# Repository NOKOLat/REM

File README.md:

# REM (Receiver Extension Module)
本システムはs.busを読み取り最大10chのPWMを出力するものである．
一般的なFutaba製受信機では，6ch程度のものが多くまたチャンネル数を増やすと重量が増加する問題があった．
Futaba製受信機で最軽量なものはR3206SBMで公称1g以下であり，s.busと6chのPWM出力が可能である．実用時にはサーボやESCへの電源の分配を外部で行う必要があり4g程度である．その他の受信機は6chで8g，8chで10g程度となっている．
本システムは10chで5gに収まる軽量なものである．

また，飛行ロボコン マルチコプター部門の自動投下に対応するためにADCポートを1つ設けている．

# 使い方
## 基板の解説
受信機やESC，サーボなどの接続図を示す．

受信機は図上方のピンヘッダーのうち左側3ピンを使用する．
ピン配置は左からGND，5V，S.Busである．

図右側にはESC,サーボ向けのPWM出力をするピンが10ch分ある．
図下側から順に1ch - 10chである．
従来の受信機と同様にESCを接続すると基板に電源が供給される．

図左側のPC及びシリアル変換モジュールはマイコンのプログラムの書き込みに使用する．
ピンヘッダーのピン配置は上からシリアル通信のRXとTX,GND,3.3V，BOOTである．
3.3Vに電源を接続する際は基板に5Vを入力してはならない．
シリアル通信のRX，TXはいずれもマイコンのRX，TXピンに接続されている．
RXピンに信号を入力し，TXピンから信号が出力される．

インジケーターとしてLEDが4つある．
LEDはPWM用のピンヘッダーに近い方から順に，5Vと3.3Vの電源確認および2つのマイコンの状態確認用である．

## PCとの接続
プログラムの書き込みには[STM32CubeProgrammer](https://www.st.com/ja/development-tools/stm32cubeprog.html)を使用する．
STのwebページよりダウンロードし，インストールする．

使用するものはPCとシリアル変換モジュール，5V電源供給のためのLiPoおよびESCである．
まず，シリアル変換モジュールと基板でシリアル通信の信号線 (RX,TX)とGNDの3線を接続する．
その後，タクトスイッチを押しながら5Vを接続する．
最後にPCとシリアル変換モジュールを接続する．

STM32CubeProgrammerを用いてマイコンに接続する．
まず，マイコンとの接続方法をUARTに設定する．
その後，UARTの設定を行う．
ポートは環境によって異なるので，各自の環境においてシリアル変換モジュールのポートを選択する．
ボーレートは経験的に56000以下で選択するとよい．
その他の項目は特に設定する必要はない．
以上ができたらconnectする．
エラーが出た際はエラーメッセージを確認して対処する．
よくあるトラブルは基板の電源投入時にスイッチを上手く押せていないことなので，電源を入れ直すと解決することがある．

## 初回セットアップ
ここでは，マイコンのプログラムに依存しない部分の設定をおこなう．
このステップを正しく実行しないと，プログラムの書き直しが不可能になるので確実に行う．

画面左のメニューから**OB**(Option bytes)を選択する．
**User Configuration**にある**nBOOT_SEL**および**nBOOT1**，**nBOOT0**のチェックが画像と同じになるように設定する．

同様に**NRST_MODE** を2に設定する．

以上でセットアップは完了である．

## プログラムの更新
画面左のメニューよりErasing & Programmingを選択する．
File Pathで実行ファイル (10chReceiver.elf) を選択する．
**Verify programming**と**Run after programming**にチェックを入れる．
**Start Programming**をクリックして，書き込みを開始する．
処理が終了し，Logに`Download verified successfully`と表示されていれば正常終了である．

実行ファイルはGithubのリリースよりダウンロードするか，ソースファイルをビルドして用意する．

## LEDの点滅パターン
プログラム起動時にLED1とLED2が点灯し起動処理が完了すると消灯するが，点灯時間がごく短時間であるため確認できないと思われる．
s.busのフレームを受信している間はLED2が高速で点滅する．
受信データがフェイルセーフもしくはフレームロストを示していたり，正常にデータを処理できない状態が続くとLED1がゆっくり点滅する．
また，s.busの受信ができない状態となったときもLED1がゆっくり点滅する．
したがって，LEDの点灯パターンを用いておおよそ下記のように判断できる．

|LED(Green)|LED(Red)|Stat|
|:--:|:--:|:--:|
|早い点滅|消灯|正常|
|遅い点滅|点灯|基板-受信機の接続に問題がある|
|早い点滅|点灯|受信機-プロポの通信に問題がある|

# ファームウェアのカスタマイズ
## PWMデューティー比レンジの設定
Futaba製RCサーボ向けのPWM出力とLED向けにデューティー比0%から100%の2種類を用意している．
設定は *user.h* にある`convertToPulseWidth()`で行う．
使用方法は実装を見てほしい．
RCサーボ向けのPWMとする場合は`CONVERT_TO_RC_PWM_WIDTH(sbusValue)`を使用する．
LED向けにデューティー比を0%から100%とする場合は`CONVERT_TO_LED_PWM_WIDTH(sbusValue)`を使用する．

## カスタムミキシング
*user.h* にある`mixer()`で行う．
ユーザーは`mixer()`を編集することにより，ミキシングや条件に応じた動作の変更をすることができる．

アナログ入力を使用する場合はadcValueを参照する．
ADCは0から3.3Vの入力を0から255のディジタル値に変換するように設定されているのでadcValueの値域は0から255となる．
フォトトランジスタとアナログ入力を使用することで，マルチコプター部門の自動投下に対応可能である．

# 基板
PCBデザインは *./PCB/* にある．

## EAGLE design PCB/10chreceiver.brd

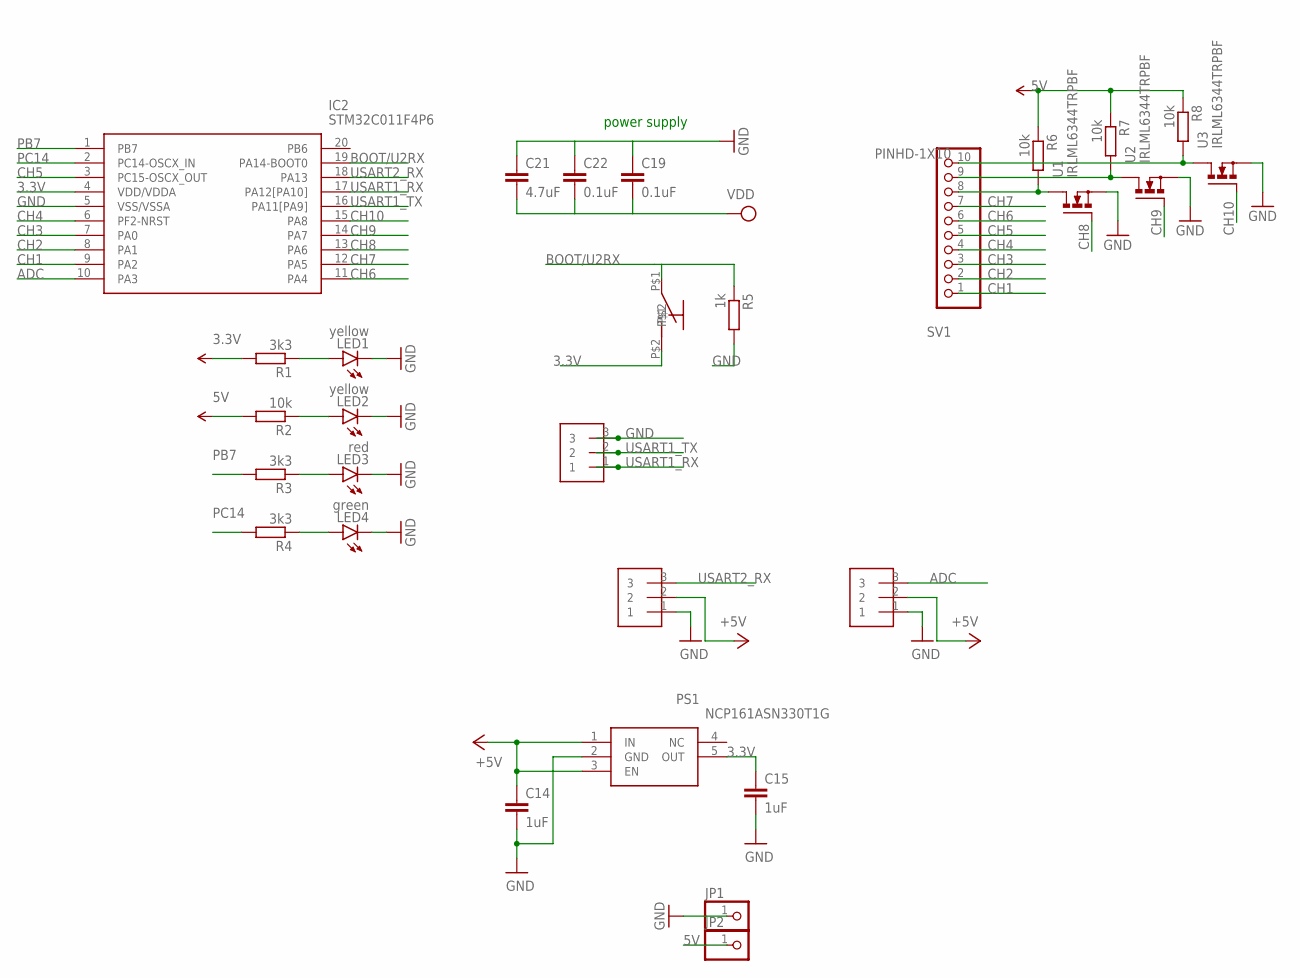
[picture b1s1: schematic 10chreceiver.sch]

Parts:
C14, C15: 1uF; C1608
C19, C22: 0.1uF; C1608
C21: 4.7uF; C1608
CN1, CN2, CN3: 1X3
IC2: STM32C011F4P6; SOP65P640X120-20N
JP1, JP2: PINHD-1X1; 1X01
LED1, LED2: yellow; CHIPLED_0603
LED3: red; CHIPLED_0603
LED4: green; CHIPLED_0603
PS1: NCP161ASN330T1G; SOT95P280X145-5N
R1, R3, R4: 3k3; R0603
R2, R6, R7, R8: 10k; R0603
R5: 1k; R0603
SV1: PINHD-1X10; 1X10-BIG
SW2: TSY3420-TACTSW
U1, U2, U3: IRLML6344TRPBF; SOT95P240X112-3N

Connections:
3.3V: C15.1, C19.2, C21.2, C22.2, IC2.4 (VDD/VDDA), PS1.5 (OUT), R1.2, SW2.P$2
5V: C14.1, CN2.2, CN3.2, JP2.1, PS1.1 (IN), PS1.3 (EN), R2.2, R6.1, R7.1, R8.1
ADC: CN2.3, IC2.10 (PA3)
BOOT/U2RX: IC2.19 (PA14-BOOT0), R5.1, SW2.P$1
CH1: IC2.9 (PA2), SV1.1
CH2: IC2.8 (PA1), SV1.2
CH3: IC2.7 (PA0), SV1.3
CH4: IC2.6 (PF2-NRST), SV1.4
CH5: IC2.3 (PC15-OSCX_OUT), SV1.5
CH6: IC2.11 (PA4), SV1.6
CH7: IC2.12 (PA5), SV1.7
CH8: IC2.13 (PA6), U1.1 (G)
CH9: IC2.14 (PA7), U2.1 (G)
CH10: IC2.15 (PA8), U3.1 (G)
GND: C14.2, C15.2, C19.1, C21.1, C22.1, CN1.3, CN2.1, CN3.1, IC2.5 (VSS/VSSA), JP1.1, LED1.C, LED2.C, LED3.C, LED4.C, PS1.2 (GND), R5.2, U1.2 (S), U2.2 (S), U3.2 (S)
unnamed: LED3.A, R3.1
unnamed: LED4.A, R4.1
unnamed: R6.2, SV1.8, U1.3 (D)
unnamed: LED1.A, R1.1
unnamed: R7.2, SV1.9, U2.3 (D)
unnamed: R8.2, SV1.10, U3.3 (D)
unnamed: LED2.A, R2.1
PB7: IC2.1 (PB7), R3.2
PC14: IC2.2 (PC14-OSCX_IN), R4.2
USART1_RX: CN1.1, IC2.17 (PA12[PA10])
USART1_TX: CN1.2, IC2.16 (PA11[PA9])
USART2_RX: CN3.3, IC2.18 (PA13)

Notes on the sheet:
power supply

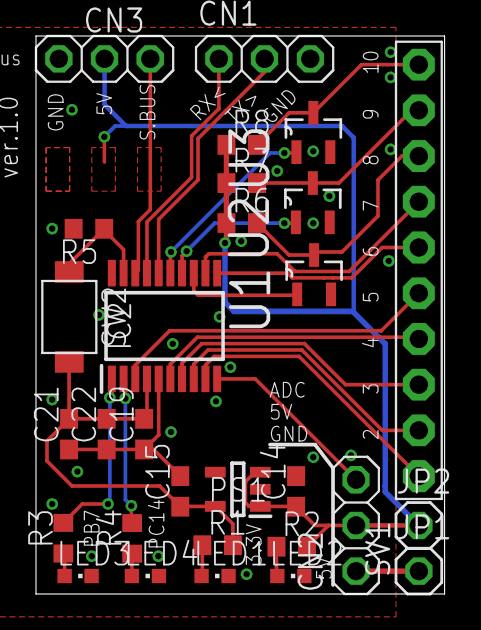
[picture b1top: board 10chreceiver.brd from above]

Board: 2 copper layers, 22.7 x 31.0 mm, 29 parts (0 on the bottom side), 27 nets.

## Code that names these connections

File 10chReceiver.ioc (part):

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Mcu.Name=STM32C011F(4-6)Px
Mcu.Package=TSSOP20
Mcu.UserName=STM32C011F4Px
PA0.Signal=S_TIM16_CH1
PA1.GPIOParameters=GPIO_ModeDefaultPP,GPIO_Speed,PinState,GPIO_PuPd
PA1.GPIO_ModeDefaultPP=GPIO_MODE_AF_PP
PA1.GPIO_PuPd=GPIO_NOPULL
PA1.GPIO_Speed=GPIO_SPEED_FREQ_LOW
PA1.PinState=GPIO_PIN_RESET
PA1.Signal=S_TIM1_CH2
PA10\ [PA12].Mode=Asynchronous
PA10\ [PA12].Signal=USART1_RX
PA13.Mode=Asynchronous
PA13.Signal=USART2_RX
PA14-BOOT0.Mode=Asynchronous
PA14-BOOT0.Signal=USART2_TX
PA2.Signal=S_TIM1_CH3
PA3.Mode=IN3
PA3.Signal=ADC1_IN3
PA4.Signal=S_TIM14_CH1
PA5.Signal=S_TIM1_CH1
PA6.Signal=S_TIM3_CH1
PA7.Signal=S_TIM3_CH2
PA8.Signal=S_TIM3_CH4
PA9\ [PA11].Mode=Asynchronous
PA9\ [PA11].Signal=USART1_TX
PB7.Signal=GPIO_Output
PC14-OSCX_IN\ (PC14).Signal=GPIO_Output
PC15-OSCX_OUT\ (PC15).Signal=S_TIM3_CH3
PF2-NRST.Signal=S_TIM1_CH4
RCC.HSE_VALUE=8000000
RCC.SYSCLKFreq_VALUE=48000000
board=custom

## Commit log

2024-08-16 とりあえず動いた
2024-08-16 refactor
2024-11-22 fix bug
2025-05-25 bug fix
2025-05-25 update user action for cross environments
2025-05-25 update module
2025-05-25 debugした
2025-05-27 write README.md
2025-05-29 Create LICENSE
2025-06-09 start development of v2
2025-06-09 finish coding
2025-06-28 一般班向けのデバック終了
2025-06-28 add MCU_OB (Option Bytes) configuration file
2025-07-01 adc関連のdebug 飛行機向けの動作確認
2025-08-16 update lib
2025-08-16 debug
2025-08-16 カスタマイズ
2025-09-01 custom
2025-09-03 プロポ - 受信機の通信が切断されたときフェイルセーフが機能するように修正
2025-09-04 arranged
2025-09-09 LED点灯用に9, 10chのデューティー比レンジを変更
2025-09-21 手動モードでの赤外線検知後にホールド
2025-10-01 #8 PWMパルス幅の切り替え
2025-10-01 editing
2025-10-05 デューティー比の切り替えについて書ききった
2025-10-05 remove comment-out
2025-10-05 PCBについて追記
2025-10-05 upload PCB design
2025-10-05 sbusライブラリの更新
2025-10-05 rename ioc file

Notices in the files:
parts and their libraries:
SparkFun-PowerSymbols: Licensing: Creative Commons ShareAlike 4.0 International - https://creativecommons.org/licenses/by-sa/4.0
